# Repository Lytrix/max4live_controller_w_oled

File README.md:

# Max4Live Magnetic Encoder controller with oled screen 

This repository contain the files to be able to create a Max4live 4 controller with Oled as a 5HP Eurorack module to control your VST plugins.

This setup can easily be extended to a 4 units by using jumper cables on the same pcb together with the headers on the boards to maximize a 5 panel order from jlcpcb.

### How to install & use ###

1. Download this repo
2. Open the Arduino code and upload to the Teensy
3. Copy the `Max4Live Controller & Hub` folder to `/Music/Ableton/User Library/Presets/Audio Effects`
4. Open Ableton and place the `Max4live Serial Hub OSC.amxd` to the master channel and select your Teensy device.
5. Place `Max4live Controller OSC.amxd` on to the track you want to control
6. Select the VST device in the pull down menu which you want to control
7. Select the parameters for each potentiometer and button row.

### History ###

After using excelent Eurorack Droid system and having created my own Launchpad type solution on it, I wanted to have more hands on controllers also for my VST plugins within Ableton.

I really like the SSL suite of EQ's so I first looked at the UC1, As it was too big to fit in my small studio, I decided to build my own eurorack version to fit into my controller case with visual feedback to limit having to look at the DAW screen when adjusting EQ. 

#### MIDI? ####
I discovered early on the 127 midi steps were not fine grained enough.
Even using the pitchbend range or using MSB/LSB (sending on CC1 + CC 32) were often with issues still:
1. Still quite noisy with an analog encoder so hard to dail in precise values
2. Ableton could not set a parameter as 14bit midi 

So after some experimentation I decided to go with using an 3 euro AS5600 magnetic encoder and a cheap 0.75 Euro EC11 encoder to get a noise free 12bit 4096 step resolution which was precise enough to dail precise frequencies using this video as an example:
https://www.youtube.com/watch?v=1UmqNF65rck

This worked surpisingly well and is a great hack!

#### Breadboard tests and hacking the potentiometer to work with the magnetic encoder ####

#### SYNC mouse and controller input ####
The next challenge was to ensure the encoder did not switch back to 0 halfway if the parameter changed via mouse input or when the parameter type changed. 
The solution was to set the offset of the magnetic encoder chip when the value changed externally. That way the encoder is always in sync before it adjusts it's value.

I coded a piece of logic to ensure whenever the value of the encoder is outside of +-2 numbers, MaxMSP sends an offset value update to the Teensy. 
The encoder is only allowed to change the values when the values of the VST parameter and the AS5600 offset are the same.

Th next challenge was to ensure the value was updated before the encoder could output any values. Here I got a lot of race condition issues, and it took me a week before I could tackle this. 

#### Controller & Display updates ####
For all functions I use lists to iterate over all changed values which are updated and also to set each of the AS5600 controllers and OSC adresses within different functions. This makes the code more DRY and makes it easier to add more parameters.

I created one function to gather all values to be displayed which loops in the main loop of the Arduino code.
I also created one function to set all updates from the encoders
And created one function to parse to each specific OSC address recieving part. 

### Parts list ###
- 1 Teensy 4.0 with headers
- 4-16 [AS5600 magnetic angle sensors](https://www.tinytronics.nl/shop/en/sensors/magnetic-field/as5600-magnetic-angle-sensor-encoder-module)
- 4-16 [EC11 rotary encoders](https://www.tinytronics.nl/shop/en/switches/manual-switches/rotary-encoders/rotary-encoder-ec11-20mm)
- 1-4 [25mm wide SSD1306 Oled Screens](https://www.ebay.com/itm/145136236774), or [Gadgetbouw.nl](https://www.gadgetbouw.nl/shop/0-96inch-128x64-i2c-oled-scherm-ssd1306-wit-of-blauw/) Check if they are really 25mm in width visible by the mounting holes being directly to the end of the pcb on both sides. Most cheap SSD1306 Oleds are 27mm.
- 1-5 PCB boards from jlcpcb
- 1-5 Alu front panels from jlcpcb
- Header pins and sockets
- [M3 nylon spacers 6mm](https://www.amazon.nl/dp/B07CG7F2YL?psc=1&ref=ppx_yo2ov_dt_b_product_details)
- [M3 nylon nuts](https://www.amazon.nl/dp/B07CG4C5QY?psc=1&ref=ppx_yo2ov_dt_b_product_details)
- 1 Superglue for mounting magnets and spacers
- 2-8 pushbuttons [EAO](https://www.techniekwebshop.nl/eao-benelux-serie-19-drukknop-9x9-puls-1m-verlicht-verkoop-per-1-x-1-stuk-19-451-035-7011339-type-knop-hoog-kleur-knop-zonder-toetsenplaat-bouwvorm-lens-vierkant-gatdiameter-8-mm-breedte-opening-0-mm-hoogte-opening-0-mm-geschikt-voor-verlichting.html) or cheaper 9.2mm types from [Ebay](https://www.ebay.com/itm/154221529860?hash=item23e851cb04:g:r4gAAOSwfl1gFLhZ&amdata=enc%3AAQAIAAAAwH2u8qPl33Nu%2BKZJNMI1XoYbnsN1xgGI8EFPX4nB848Pm47jGUqLpj%2F8kNmLPnr4k61d1Jy8z%2B8IwcQQGUOk3j0dQ3JgpBgDFUv3wmNJlS293fUbqb7MbdbXtsG7Uovn64k0coLJQ3QYye3IVVsqrKsjZNJoqrGjTdVRb0ej1huffO7VVyLBjE%2BA2dLggxsoLtFlr8CELEeITrrbJl9YzDZL0jUuFreZLzMQduZDw08uBwdF%2BrDNQ3BtSAdQ1724Lw%3D%3D%7Ctkp%3ABk9SR9yUlfSAYw) 

## Software ##

The software side consists on 2 pieces of code. One for the Teensy and one for Max4live.

I tested first a simple setup with using the standard serial ASCII communication, but found it quite fiddly to ensure to retrieve each different piece of information being send.
The [Open Sound Control (OSC)](https://opensoundcontrol.stanford.edu/spec-1_0.html) addressing structure felt like a much more robust way to send information back and forth, but unfortunately the OSC library from [CNMAT](https://github.com/CNMAT/OSC) did not work properly any more in the current MaxMSP and via serial (instead of network port). After a lot of research I finally found a good working library to make this work on the Teensy with MaxMSP (jey!):
https://github.com/thomasfredericks/MicroOsc

### Research documentation ###

Max4Live using more than 1 instance fix: add r --- to create random unique numbers
https://cycling74.com/forums/multiple-max4live-instances

Serial input Teensy to MaxMSP
https://www.youtube.com/watch?v=6bT3G4Mep7E

Serial output MaxMSP to Teensy
https://www.youtube.com/watch?v=68L-WHh3Ows

Button switch using internal pull up:
https://www.pjrc.com/teensy/td_digital.html  

MaxMSP scaling log
https://cycling74.com/forums/vst-plugin-parameter-scaling-problem

Dynamically load bpatchers:
https://cycling74.com/forums/dynamically-created-sub-patchersbpatches

Dummy virtual Serial
https://arduino.stackexchange.com/questions/9857/can-i-make-the-arduino-ignore-serial-print

Best example with many displays
https://www.youtube.com/watch?v=XFh9ZhL0jhE

Control Surface library struggle
https://github.com/tttapa/Control-Surface/issues/286

Good example to start with, also using 4 displays and using MCU:
https://projecthub.arduino.cc/criusdigitalstudio/diy-usb-midi-daw-controller-ecdcf6

good example of display fader
https://github.com/yilmazyurdakul/ArduinoOledMidiController
https://github.com/yilmazyurdakul/ArduinoOledMidiController/blob/main/ArduinoFile.ino

4 rotary encoders with midi control
http://little-scale.blogspot.com/2017/04/teensy-36-basicsusing-rotary-encoders.html

2 displays
https://www.brainy-bits.com/post/two-is-better-than-one-how-to-connect-two-spi-oled-displays

4 displays with Arduino
https://www.youtube.com/watch?v=MO6hbQcX8fE

4 displays and 4 encoders with visuals
https://projecthub.arduino.cc/yilmazyurdakul/arduino-midi-controller-with-encoder-oled-display-eeprom-311960

### Libraries ###
display https://www.pjrc.com/teensy/td_libs_SSD1306.html
encoder https://www.pjrc.com/teensy/td_libs_Encoder.html
endless potentiometer: https://github.com/juanlittledevil/EndlessPotentiometer
noise reducer analog signal: https://github.com/dxinteractive/ResponsiveAnalogRead

scroll text example:
https://stackoverflow.com/questions/40564050/scroll-long-text-on-oled-display

midi https://github.com/tttapa/Control-Surface

## LCD suggestions ###
http://midibox.org/forums/topic/29225-modul-box-ng-v2/?do=findComment&comment=199453

Oled display <25mm height
https://www.winstar.com.tw/products/oled-module/graphic-oled-display/sh1106-oled.html

multiplexer met tutorial (zie ook youtube filmpje)
https://www.tinytronics.nl/shop/nl/communicatie-en-signalen/io-converters/i2c-multiplexer-tca9548a

128 pulse encoder (too expensive)
https://nl.mouser.com/datasheet/2/54/ace-777357.pdf

1024 to 256 midi values with 10 bit nano:
https://forum.arduino.cc/t/potentiometer-send-midi-cc/142766/7

analog potentiometer Kore2:
https://hackaday.io/project/171841-driveralgorithm-for-360-deg-endless-potentiometer
with: https://nl.mouser.com/ProductDetail/Alpha-Taiwan/RV112FF-40B3N22F0B10K?qs=Znm5pLBrcAJwOGngbhkPgg%3D%3D

more examples:
https://diyelectromusic.wordpress.com/2021/09/28/arduino-midi-rotary-encoder-controller/

magnetic encoder:
https://curiousscientist.tech/blog/as5600-magnetic-position-encoder

working magnetic encoder example
https://www.youtube.com/watch?v=1UmqNF65rck

Bourns dail 20 turn
https://www.zendamateur-marktplaats.nl/componenten/componenten-anders/bourns-dial-model-h-46-36496.html

potential bigger potentiometer:
https://www.gear4music.com/Guitar-and-Bass/Emerson-Custom-CTS-250K-Short-Split-Shaft-Pro-Potentiometer/1GAA

Encoder example fast/slow relative unsigned bit:
https://remotify.io/community/question/absolute-14-bit

OSC
https://github.com/CNMAT/OSC/blob/master/examples/SerialOscuinowithMessages/SerialOscuinowithMessages.ino
https://www.ableton.com/en/packs/connection-kit/
https://github.com/thomasfredericks/MicroOsc

https://forum.arduino.cc/t/slipserial-and-osc-but-generally-reading-serial-across-loop-s/563369

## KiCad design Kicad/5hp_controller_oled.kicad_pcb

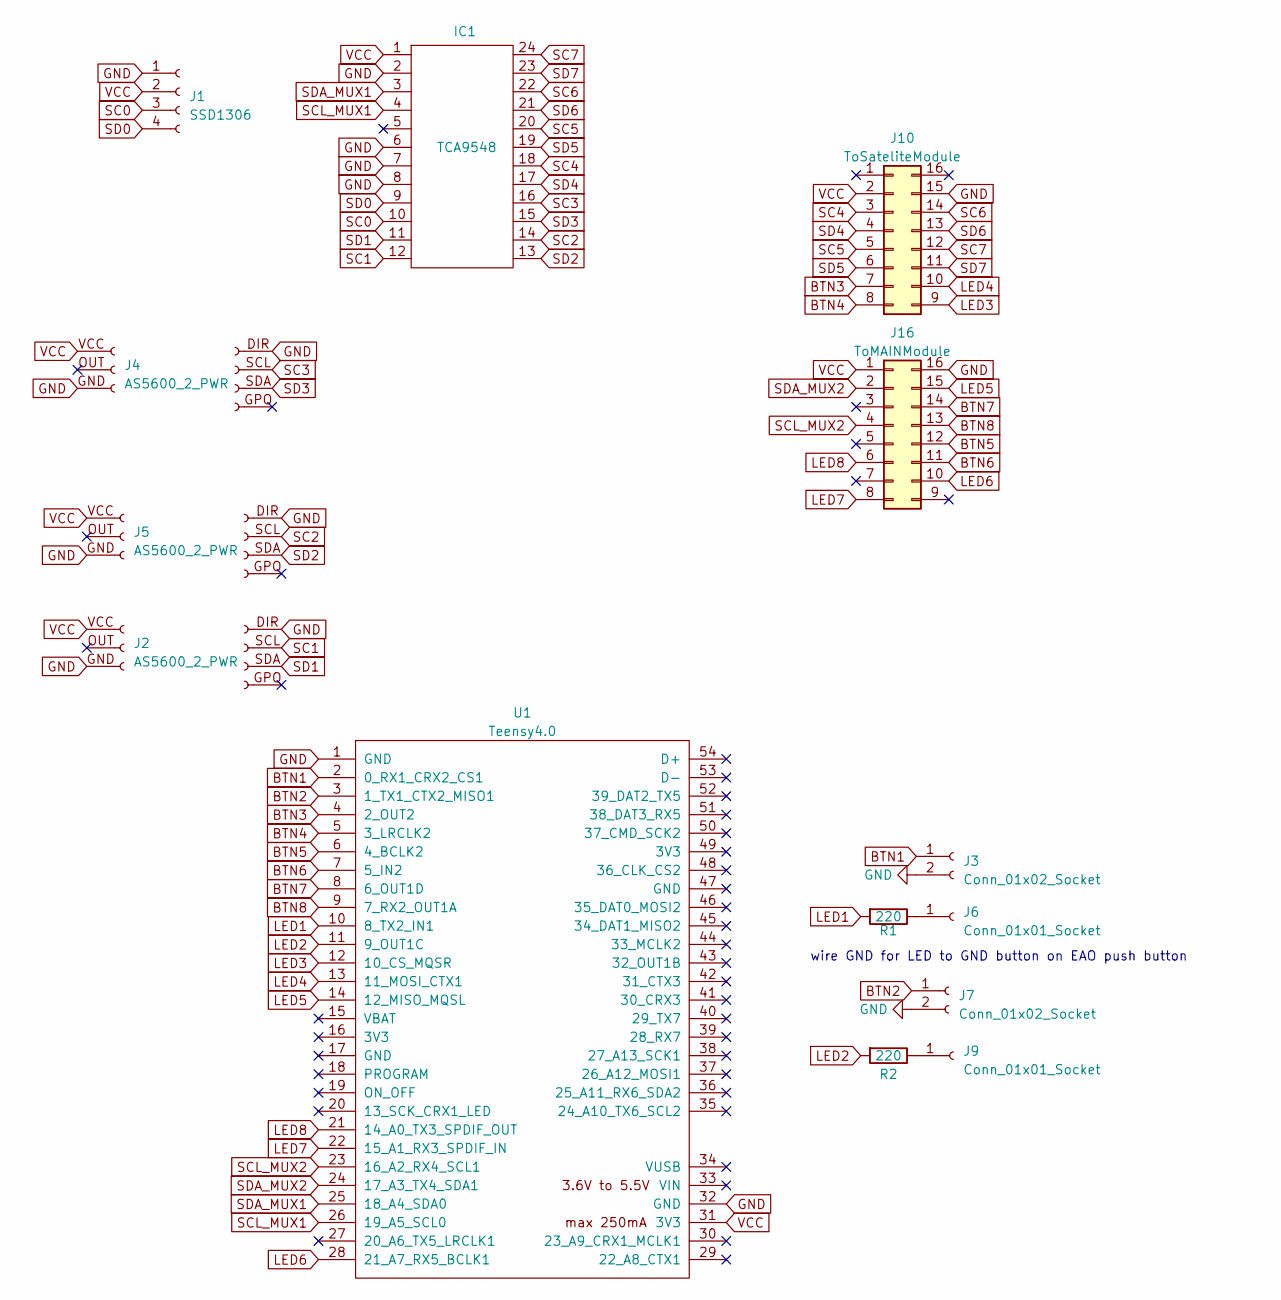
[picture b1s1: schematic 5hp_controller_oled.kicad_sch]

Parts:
IC1: TCA9548; DIP-24_W9.xx mm_Socket
J1: SSD1306; 128x64OLED_25mm
J2, J4, J5: AS5600_2_PWR; AS5600
J3, J7: Conn_01x02_Socket; PinHeader_1x02_P2.54mm_Vertical
J6, J9: Conn_01x01_Socket; PinHeader_1x01_P2.54mm_Vertical
J10: ToSateliteModule; PinSocket_2x08_P2.54mm_Vertical
J16: ToMAINModule; PinSocket_2x08_P2.54mm_Vertical
R1, R2: 220; R_0603_1608Metric_Pad0.98x0.95mm_HandSolder
U1: Teensy4.0; Teensy40_SMT

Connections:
BTN1: J3.1, U1.2 (0_RX1_CRX2_CS1)
BTN2: J7.1, U1.3 (1_TX1_CTX2_MISO1)
BTN3: J10.7, U1.4 (2_OUT2)
BTN4: J10.8, U1.5 (3_LRCLK2)
BTN5: J16.12, U1.6 (4_BCLK2)
BTN6: J16.11, U1.7 (5_IN2)
BTN7: J16.14, U1.8 (6_OUT1D)
BTN8: J16.13, U1.9 (7_RX2_OUT1A)
GND: IC1.2 (GND), IC1.6 (A0), IC1.7 (A1), IC1.8 (A2), J1.1, J2.DIR (Pin_4), J2.GND (Pin_3), J3.2, J4.DIR (Pin_4), J4.GND (Pin_3), J5.DIR (Pin_4), J5.GND (Pin_3), J7.2, J10.15, J16.16, U1.1 (GND), U1.32 (GND)
LED1: R1.2, U1.10 (8_TX2_IN1)
LED2: R2.2, U1.11 (9_OUT1C)
LED3: J10.9, U1.12 (10_CS_MQSR)
LED4: J10.10, U1.13 (11_MOSI_CTX1)
LED5: J16.15, U1.14 (12_MISO_MQSL)
LED6: J16.10, U1.28 (21_A7_RX5_BCLK1)
LED7: J16.8, U1.22 (15_A1_RX3_SPDIF_IN)
LED8: J16.6, U1.21 (14_A0_TX3_SPDIF_OUT)
unnamed: J6.1, R1.1
unnamed: J9.1, R2.1
SC0: IC1.10 (SC0), J1.3
SC1: IC1.12 (SC1), J2.SCL (Pin_5)
SC2: IC1.14 (SC2), J5.SCL (Pin_5)
SC3: IC1.16 (SC3), J4.SCL (Pin_5)
SC4: IC1.18 (SC4), J10.3
SC5: IC1.20 (SC5), J10.5
SC6: IC1.22 (SC6), J10.14
SC7: IC1.24 (SC7), J10.12
SCL_MUX1: IC1.4 (SCL), U1.26 (19_A5_SCL0)
SCL_MUX2: J16.4, U1.23 (16_A2_RX4_SCL1)
SD0: IC1.9 (SD0), J1.4
SD1: IC1.11 (SD1), J2.SDA (Pin_6)
SD2: IC1.13 (SD2), J5.SDA (Pin_6)
SD3: IC1.15 (SD3), J4.SDA (Pin_6)
SD4: IC1.17 (SD4), J10.4
SD5: IC1.19 (SD5), J10.6
SD6: IC1.21 (SD6), J10.13
SD7: IC1.23 (SD7), J10.11
SDA_MUX1: IC1.3 (SDA), U1.25 (18_A4_SDA0)
SDA_MUX2: J16.2, U1.24 (17_A3_TX4_SDA1)
VCC: IC1.1 (VCC), J1.2, J2.VCC (Pin_1), J4.VCC (Pin_1), J5.VCC (Pin_1), J10.2, J16.1, U1.31 (3V3)

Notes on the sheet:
wire GND for LED to GND button on EAO push button

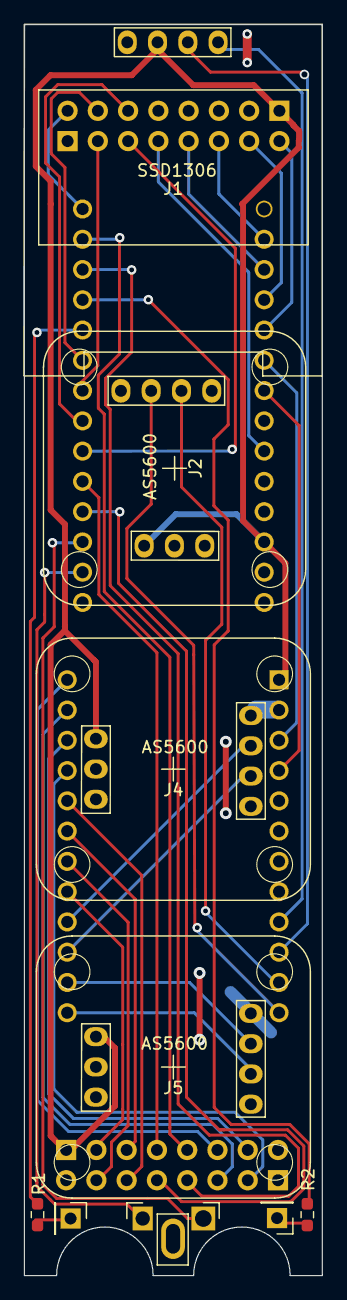
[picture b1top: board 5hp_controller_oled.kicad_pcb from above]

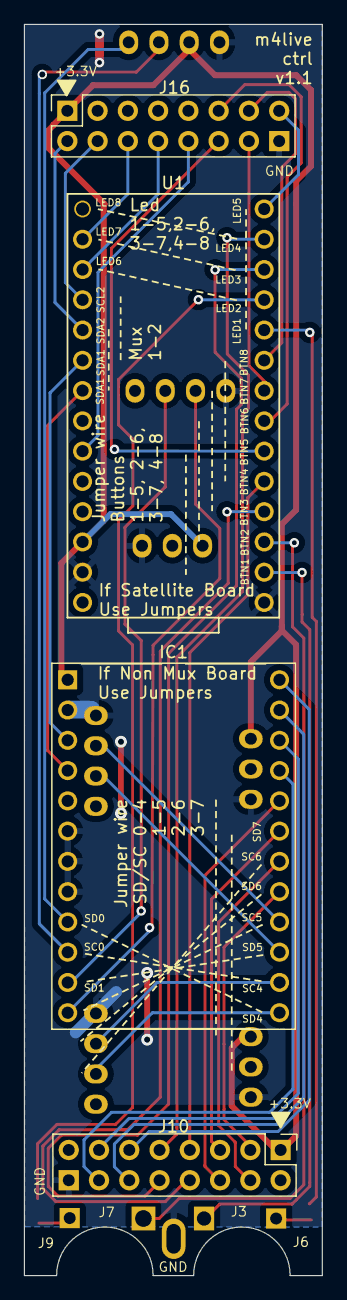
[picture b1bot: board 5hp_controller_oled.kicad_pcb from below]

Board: 2 copper layers, 25.0 x 105.0 mm, 14 parts (4 on the bottom side), 40 nets.

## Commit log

2023-11-24 Working single version, but still laggy
2023-11-24 Added offset retry logic
2023-11-24 Working 2 VSTs switching, using delay on pot send messages
2023-11-24 bpatcher from Parameter_selector
2023-11-24 Added arduino teensy code
2023-11-24 cleanup foldername
2023-11-24 Select VST3 added
2023-11-24 Updated Styling and parameter update when VST changed
2023-11-29 Added kicad code and updated Readme
2023-11-29 Added more visuals
2023-11-29 fixed url images
2023-11-29 fixed capital
2023-11-29 images encoder
2023-11-29 updated panel
2023-11-29 Added VST screenshot
2023-11-29 rephrashed intro
2023-11-29 patched type select naming
2023-11-29 Final pcb and frontpanel
2023-11-30 Added temp supports for screen opening to prevent crack during manufacturing
2023-12-23 Reverted back to working Max4live version
2023-12-23 Set title caused isse, moved sliders to end with println
2023-12-23 Revert back display layout, added button setup Max4live
2023-12-23 Fixed Screen flickering, reverted back display setup
2023-12-23 fixed laggy display using 1M refresh
2023-12-23 last tweak display speed
2023-12-26 Fully working patch, only led update from VST remains.
2023-12-27 Optimized led button behaviour
2023-12-29 Prep for second cntrl
2024-01-02 Switch Track working again
2024-01-03 Select Track ID working, fixed hanging Max 8.5 v10
2024-01-03 Fixed too slow updating offset
2024-01-03 Increased chunk size to 512 for smoother updates
2024-01-03 Prepared second tca module logic
2024-01-06 Lower update speed display, added 3rd controller
2024-01-09 Added 4th module
2024-01-09 Removed automatic opened and checklist menu from Serial as partial fix hanging Max.
2024-01-09 Reduced millis from 50>10 for sending serial faster to speed up display update
2024-01-12 Replaced serial logic with OSC CNMAT & test version OSC_tester (does recieve, does not send)
2024-01-12 Small tweaks to improve initial display update
2024-01-12 added photo of final modules
2024-01-12 added side photo
2024-01-13 Improved initial display all items
2024-01-13 tweaked delay bangs, to update when track switches
2024-01-13 Fixed pcb errors (wrong footprint TCA, freed up pin 13)
2024-01-13 cleanup lock file and backup zip
2024-01-14 Changed char array to string to reduce memory hangups
2024-01-14 Switched to OSC message list and 1MHz oleds
2024-01-14 flipped float-string to string-float list, to fix empty strings
2024-01-14 Cleaned up naming of bpatchers
2024-01-15 Set Global serial send/receive and optimised track switching
2024-01-15 Cleanup arduino code, changed order of controllers
2024-01-15 more cleanup, changes string to char strcpy button
2024-01-15 Fix refresh and center Title
2024-01-15 cleanup arduino folders
2024-01-15 Fixed LF Gain regex to show db' ' ' '
2024-01-15 Added invert option
2024-01-16 Changed all receiving osc messages to typetags like: /value 1 2 "FREQ" 0.1
2024-01-16 Fixed -1 parameter error button and added invert option button
2024-01-16 cleanup variables
2024-01-16 tweaked the microosc buffer to have less stutter in the potentiometer after a while
2024-01-16 Removed for loop in sending oscMessages from Arduino
2024-01-16 Buttonvalues now updating correctly when switching tracks in Ableton
2024-01-16 Fixed wrong array as5600 numbers on controller 2
2024-01-16 Fixed array iteration where -1 is used
2024-01-16 Updated microOsc library to use checkOscAddressAndTypeTags
2024-01-16 Used counting fromm 0 to simplify the array selection
2024-01-16 removed for loop from updateDisplay() to fix wrongly updated sliders at initial update
2024-01-16 Reverted back to stable version and c/1/p/1 instead of c/0/p/0
2024-01-17 Fixed button updates on track switching
2024-01-17 added extra track selected gate on input vst to ensure reducing hangups
2024-01-18 UI update to show status
2024-01-18 Set unsigned int where applicable + basic screensaver
2024-01-18 Renamed max4live folder and added install instructions
2024-01-18 Created Tabs for each controller + Startup screen
2024-01-18 Fixed broken maxpat file and added example song
2024-01-19 Fixed opening VST, duplicated parameter lists, updated example file with 4K E
2024-01-21 Load initial settings with save option for each VST
2024-01-21 renumbered prepped init settings pattrstorage, removed json using m4live save logic
2024-01-21 VST snapshot now not overwritten, pattr sets parameter values without sending
2024-01-22 working save/reload selected_vst state
2024-01-22 Finally properly restore state of device after opening song
2024-01-22 Added SSL 4K B default values
2024-01-22 UI alignment and Ableton fonts
2024-01-22 increase margins save button
2024-01-22 Switched to microosc Serial to work with Max 8.6.0
2024-01-22 Fixed regression recall params on load
2024-01-23 Fixed wrong value override button setting when flipping A/B
2024-01-23 Fixed update slider value when switching A/B
2024-01-23 Fixed kHz/Hz unit selection on High/Low/LMF Freq
2024-01-23 Added Range, Trim, Release, Hold, Threshold units
2024-01-23 Fixed valus overridden by AB switch
2024-01-23 Use generated switch id instead of static number
2024-01-23 Read send value from button state to set AB switch
2024-01-23 Created separate Bpatcher for AB switch
2024-01-23 removed track select, controls
2024-01-23 removed save button
2024-01-23 removed duplicate potmeter rows
2024-01-23 removed save pattr
2024-01-23 removed osc address
2024-01-23 removed osc address potmeter input
2024-01-23 removed track selected in main patch
2024-01-23 moved abswitch out of bpatcher
2024-01-23 removed ab switch return, moved load param list out of patcher
2024-01-23 moved vst select out of bpatcher
2024-01-23 removed vst select pattr
2024-01-23 moved param out of bpatcher
2024-01-23 still crashing
2024-01-23 removed text in umenu select vst
2024-01-23 removed everything with gate = 0
2024-01-23 removed select vst umenu
2024-01-23 removed umenu parameters
2024-01-23 removed pattr loader
2024-01-23 removed gate on initial load
2024-01-23 remove oscaddress creation
2024-01-23 remove all main parameter creation
2024-01-23 remove send param names
2024-01-23 cleanup
2024-01-23 added example songs
2024-01-24 increased metro from 1 to 5 microSec to reduce crashes
2024-01-24 Added AB switch to 4K E & B
2024-01-24 Fixed duplicate list, non updating slider values
2024-01-24 fixed non updating B values, changed loadbang in serial
2024-01-24 store ab switch on 4kB
2024-01-24 removed invert pos on gate release
2024-01-24 Longer loading time for parameter list by moving them more to bottom right :/
2024-01-24 added onebang for more stability in sequence
2024-01-24 Fixed closing gate on r-messages when switching B>A
2024-01-24 removed gate on track selected to update values on load
2024-01-25 Fixed missing -1 on on ctrl and param index
2024-01-25 Fixed wrong osc addresses and . to ""
2024-01-25 Used volatile arrays on rapid updating values for display
2024-01-25 send bang to value on track change
2024-01-25 fixed hanging button state on Gate Fast Attack
2024-01-25 reduced creep effect of increase/decrease due to adding offsets. delay offset 50>150 reduced margin from 5>3
2024-01-28 Fix regression non updating button values
2024-01-28 Connect/Reconnect M4L_CTRL automatically
2024-01-28 Load all settings by Sending reconnect to active track device after port is opened
2024-01-29 optimized AB-switch maxpat to be able to save again
2024-01-29 removed delay on reconnect to fix freeze on start
2024-02-01 switch startup recieve
2024-02-01 increased polling selected track
2024-02-01 removed double stored parameter pattr name
2024-02-01 removed button parameter name, removed messages
2024-02-01 hotfix buttons
2024-02-02 removed delay on button switch fixing showing osc message on display
2024-02-02 Show 4 letter param name if only one substring in param regex
2024-02-02 reduced number of bangs to button OSC message
2024-02-02 simplified serial device + added heartbeat osc message
2024-02-02 Added heartbeat osc message
2024-02-03 test puredata-serial (sending not working)
2024-02-03 reduced delay in value updates device m4live
2024-02-03 removed startup bang, removed delay and lowered number of updates on offset with bigger range
2024-02-03 reduced offset updates to reduce osc messages
2024-02-03 semi stable, removed loadbang, changed serial to qmetro
2024-02-03 tweaked delay values to update encoder in time
2024-02-04 simplified offset update
2024-02-05 big rework, simplified routing to a single object to ensure serial processing of get events
2024-02-05 Fixed wrong AB switch logic
2024-02-05 fixed wrong order out ports parameter bpatcher causing weird behaviour
2024-02-05 test live saving (not working yet)
2024-02-06 Major cleanup of patch
2024-02-06 removed parameter enabled to test snapshot saving
2024-02-06 intermediate route teensy osc messages
2024-02-06 wip all receiving messages rerouted to one router
2024-02-06 removed wrong patchcable to ab switch
2024-02-06 Changed to CNMAT serial, and changed float to int message for slider to fix double not being read by microOsc
2024-02-06 Changed float to int button osc message
2024-02-06 changed AB switch from float to int
2024-02-06 Removed -1 from oscaddress logic in teensy adding unnecessary calculation delay
2024-02-06 Removed metro and initial value load message, to become more snappier
2024-02-07 fixed initial led behaviour buttons
2024-02-07 moved vst_control updates out of parameter/button bpatch to have one gate instead of many
2024-02-07 fixed logic wrong inversion
2024-02-07 fixed digitalRead led
2024-02-07 changed pack to pak for button update
2024-02-07 moved all gates out of bpatchers so you can follow the to serial and to vst control routing
2024-02-07 bang on ab switch both ways, and reset zl change on parameters
2024-02-07 added heartbeat
2024-02-07 recall vst name after loading
2024-02-07 enabled parameter mode vst to save state in live
2024-02-08 Fixed reload param names and vst name when opening live song
2024-02-08 Recall pattr now working with separate onebang
2024-02-08 Reload params using plugin ID getter
2024-02-08 fixed broken pattr json
2024-02-08 First attempt simplified offset update logc when switching tracks
2024-02-08 Fixed loading params on non selected track, removed unused files, added example song
2024-02-10 Add reconnect/disconnect bang
    Added bang to -1 when module is disconnected to ensure the offset is send when reconnecting
2024-02-10 int to byte on invert encoder, updated pan on pattr.json
2024-02-10 fixed regression wrong value updates when track switching
2024-02-10 Improved and simplified offset update logic removing metro
2024-02-10 Fixed offset when its 4096 or 0 by validating values to be between instead of outside range
2024-02-10 Moved ctrl screens back in place
2024-02-11 align patchwires
2024-02-11 made bpatchers uniform
2024-02-11 Added more comments
2024-02-11 Created logical bounding boxes around each function
2024-02-11 more cleanup of lines and comments
2024-02-11 removed io.serial and CNMAT serial device, not working in 8.6.0
2024-02-12 Changed serial qmetro to metro and dtr 0 to 1 to remove startup hangup
2024-02-12 Fix regression getting live track id, causing params to not load when adding a new device
2024-02-12 Added init pattr when loading device
2024-02-12 Added empty param menu when initialised
2024-02-12 removed more message objects, to improve stability on initial load + select
2024-02-13 removed more messages serial device, changed int to bang on reconnect to fix loading parameter 1 index after loading
2024-02-13 Limit value update when using mouse to prevent lag on teensy, added bang update offset after mouse input to sync controller
2024-02-13 Fixed regression AB switch not updating
2024-02-15 removed double bang on pattr load B
2024-02-15 moved message /button to pack
